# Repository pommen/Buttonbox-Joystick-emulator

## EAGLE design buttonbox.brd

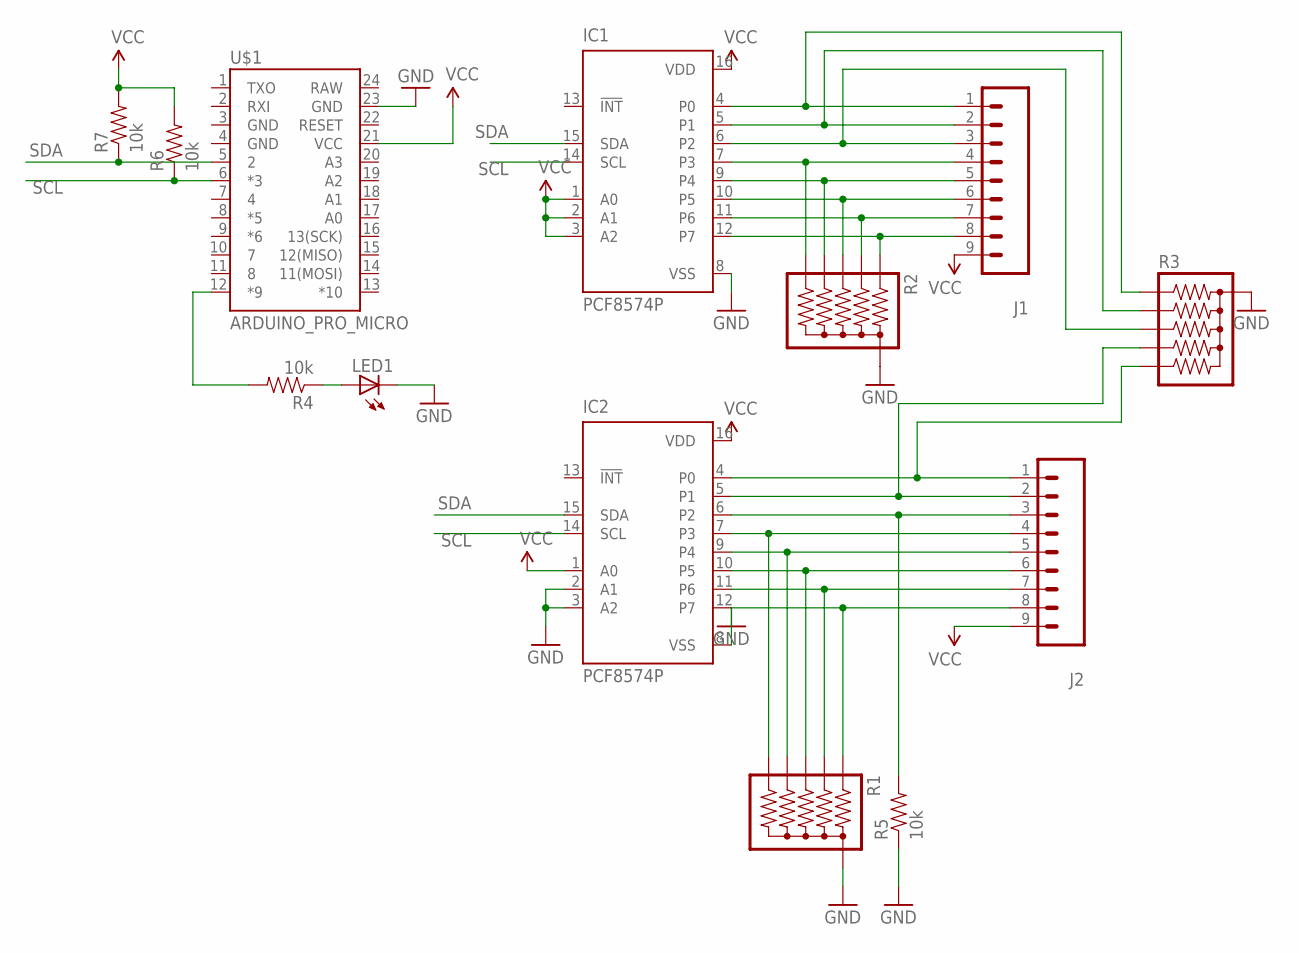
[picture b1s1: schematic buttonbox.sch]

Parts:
IC1, IC2: PCF8574P; DIL16
J1, J2: M09LONGPADS; 1X09_LONGPADS
LED1: LED5MM
R1, R2, R3: RPACK-BUSSED-5-SIP-PTH-5; RPACK-SIP-PTH-5
R4, R5, R6, R7: 10k; AXIAL-0.3
U$1: ARDUINO_PRO_MICRO

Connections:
GND: IC1.8 (VSS), IC2.2 (A1), IC2.3 (A2), IC2.8 (VSS), LED1.K (C), R1.P$1 (1), R2.P$1 (1), R3.P$1 (1), R5.P$1 (1), U$1.23 (GND)
unnamed: LED1.A, R4.P$1 (1)
unnamed: IC2.5 (P1), J2.2, R3.P$5 (5)
unnamed: R4.P$2 (2), U$1.12 (*9)
unnamed: IC2.4 (P0), J2.1, R3.P$6 (6)
unnamed: IC2.6 (P2), J2.3, R5.P$2 (2)
unnamed: IC2.7 (P3), J2.4, R1.P$6 (6)
unnamed: IC2.9 (P4), J2.5, R1.P$5 (5)
unnamed: IC2.10 (P5), J2.6, R1.P$4 (4)
unnamed: IC2.11 (P6), J2.7, R1.P$3 (3)
unnamed: IC2.12 (P7), J2.8, R1.P$2 (2)
unnamed: IC1.4 (P0), J1.1, R3.P$2 (2)
unnamed: IC1.5 (P1), J1.2, R3.P$3 (3)
unnamed: IC1.6 (P2), J1.3, R3.P$4 (4)
unnamed: IC1.7 (P3), J1.4, R2.P$6 (6)
unnamed: IC1.9 (P4), J1.5, R2.P$5 (5)
unnamed: IC1.10 (P5), J1.6, R2.P$4 (4)
unnamed: IC1.11 (P6), J1.7, R2.P$3 (3)
unnamed: IC1.12 (P7), J1.8, R2.P$2 (2)
SCL: IC1.14 (SCL), IC2.14 (SCL), R6.P$1 (1), U$1.6 (*3)
SDA: IC1.15 (SDA), IC2.15 (SDA), R7.P$1 (1), U$1.5 (2)
VCC: IC1.1 (A0), IC1.2 (A1), IC1.3 (A2), IC1.16 (VDD), IC2.1 (A0), IC2.16 (VDD), J1.9, J2.9, R6.P$2 (2), R7.P$2 (2), U$1.21 (VCC)

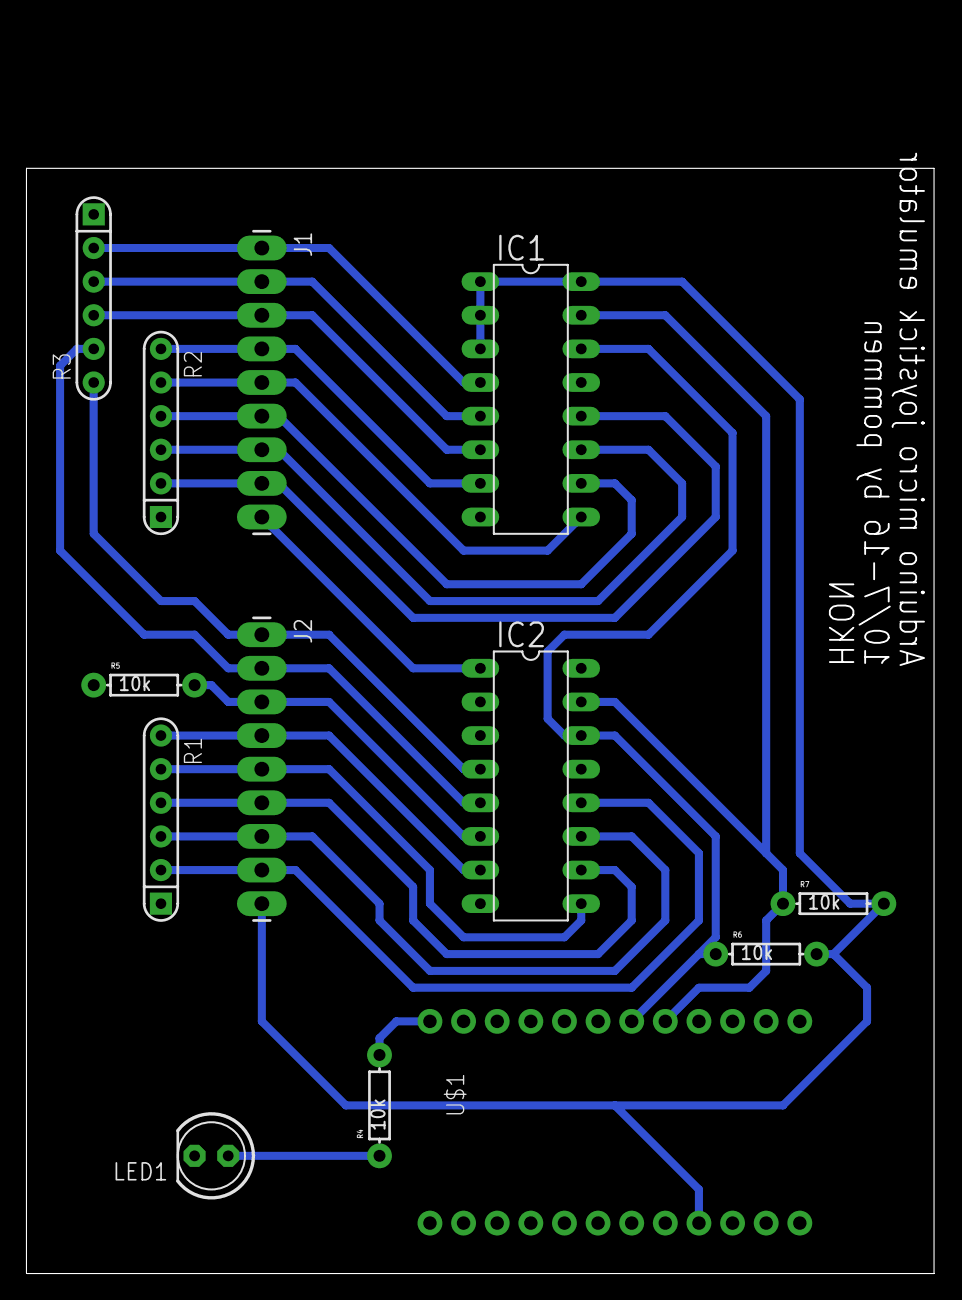
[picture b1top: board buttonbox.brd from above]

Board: 2 copper layers, 68.7 x 94.2 mm, 13 parts (0 on the bottom side), 22 nets.

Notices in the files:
parts and their libraries:
SparkFun-Boards: Licensing: Creative Commons ShareAlike 4.0 International - https://creativecommons.org/licenses/by-sa/4.0
